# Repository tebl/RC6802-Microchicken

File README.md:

# RC6802 Microchicken

When starting out with retro computers, both fictional made homebrew or the commercial ones that were actually available for purchase in the 70s and 80s, there's one book in particular I've particularly enjoyed reading - that book is "22 micro-computer projects - to build, learn and learn" by Daniel Metzger (check out [ebay](http://ebay.com) or [abebooks.com](http://abebooks.com) for a copy). Written in 1985 on the tail-end of the homebrew computer-period, it gathers what I believe is the culmination of 10 years of teaching basic electronics, digital logic and computers to people without any prior knowledge for any of those things - perfect for me!

The book builds upon each chapter by building a computer based on the 6802-processor from Motorola, a mysteriously similar processor to the now far more popular 6502. While it might be seen as an odd choice for a main processor these days, even the most advanced circuits are easily adapted to the 6502 as well. Nearly every other book I've got in my bookshelf never seem to describe much past the basics, usually circuits for storage (tape-based), single-step circuits as well as using a Video Display Generator are details left for other books to fill - this is the only book I've got that actually shows how to implement them in an easy and understandable way.

The final projects in the book result in the Microchicken-computer, which I've adapted and laid out in the form of the RC6802 Microchicken computer. I have no idea why it's called the *Microchicken*, other than that the book author obviously had a peculiar sense of humour that I can't help but agree with. My current build of the computer is shown below, I also made a short [YouTube](https://www.youtube.com/watch?v=bi4SIbvGzfI)-clip where I push some of its buttons - a whole bunch of times!

The monitor software for the RC6802 Microchicken, like the hardware design itself, is also included in the aforementioned book. I've transcribed in and slightly adapted the assembly code so that it can be assembled using modern tools, the one I've chosen to use is [SB-Assembler 3](https://www.sbprojects.net/sbasm/) as it seems to support all of the 8bit CPUs I've managed to force upon it. For a further description on the various functions of the monitor and the firmware in , see its specific [README](https://github.com/tebl/RC6802-Microchicken/tree/master/software/firmware)-file as well. 

## Modules
As with most of my computer builds the computer have been split into two required main boards to stay under the magic 5$ cost limits over at [PCBWay](https://www.pcbway.com/setinvite.aspx?inviteid=88707) for each, a CPU board as well as a UI board sandwiched on top. There may be additional modules found among the project files, but the ones I've added here are the ones that have been considered ready.

| Module             | RC6802 Microchicken        | Expanded system | Order |
| ------------------ | -------------------------- | --------------- | ----- |
| [CPU](https://github.com/tebl/RC6802-Microchicken/tree/master/RC6802%20CPU) | required | required | [PCBWay](https://www.pcbway.com/project/shareproject/RC6802_Microchicken__CPU_module_revision_B_.html?inviteid=88707) |
| [User Interface](https://github.com/tebl/RC6802-Microchicken/tree/master/RC6802%20UI) | required | required | [PCBWay](https://www.pcbway.com/project/shareproject/RC6802_Microchicken__UI_module_revision_B_.html?inviteid=88707) |
| [Backplane](https://github.com/tebl/RC6502-Apple-1-Replica/tree/master/RC6502%20Backplane) | | required | [PCBWay](https://www.pcbway.com/project/shareproject/RC6502_Apple_1_Replica__Backplane_module_revision_A_.html?inviteid=88707) |
| [Prototyping module](https://github.com/tebl/RC6502-Apple-1-Replica/tree/master/RC6502%20Prototyping) | | optional | [PCBWay](https://www.pcbway.com/project/shareproject/RC6502_Apple_1_Replica__Module_prototyping_board_.html?inviteid=88707) |

As modules are constantly being worked on, I've also added an order link to the modules so that you can always get the last version I know works. Click the module name for more information about that specific module, including schematic and the list of parts you'd need to build it (BOM).

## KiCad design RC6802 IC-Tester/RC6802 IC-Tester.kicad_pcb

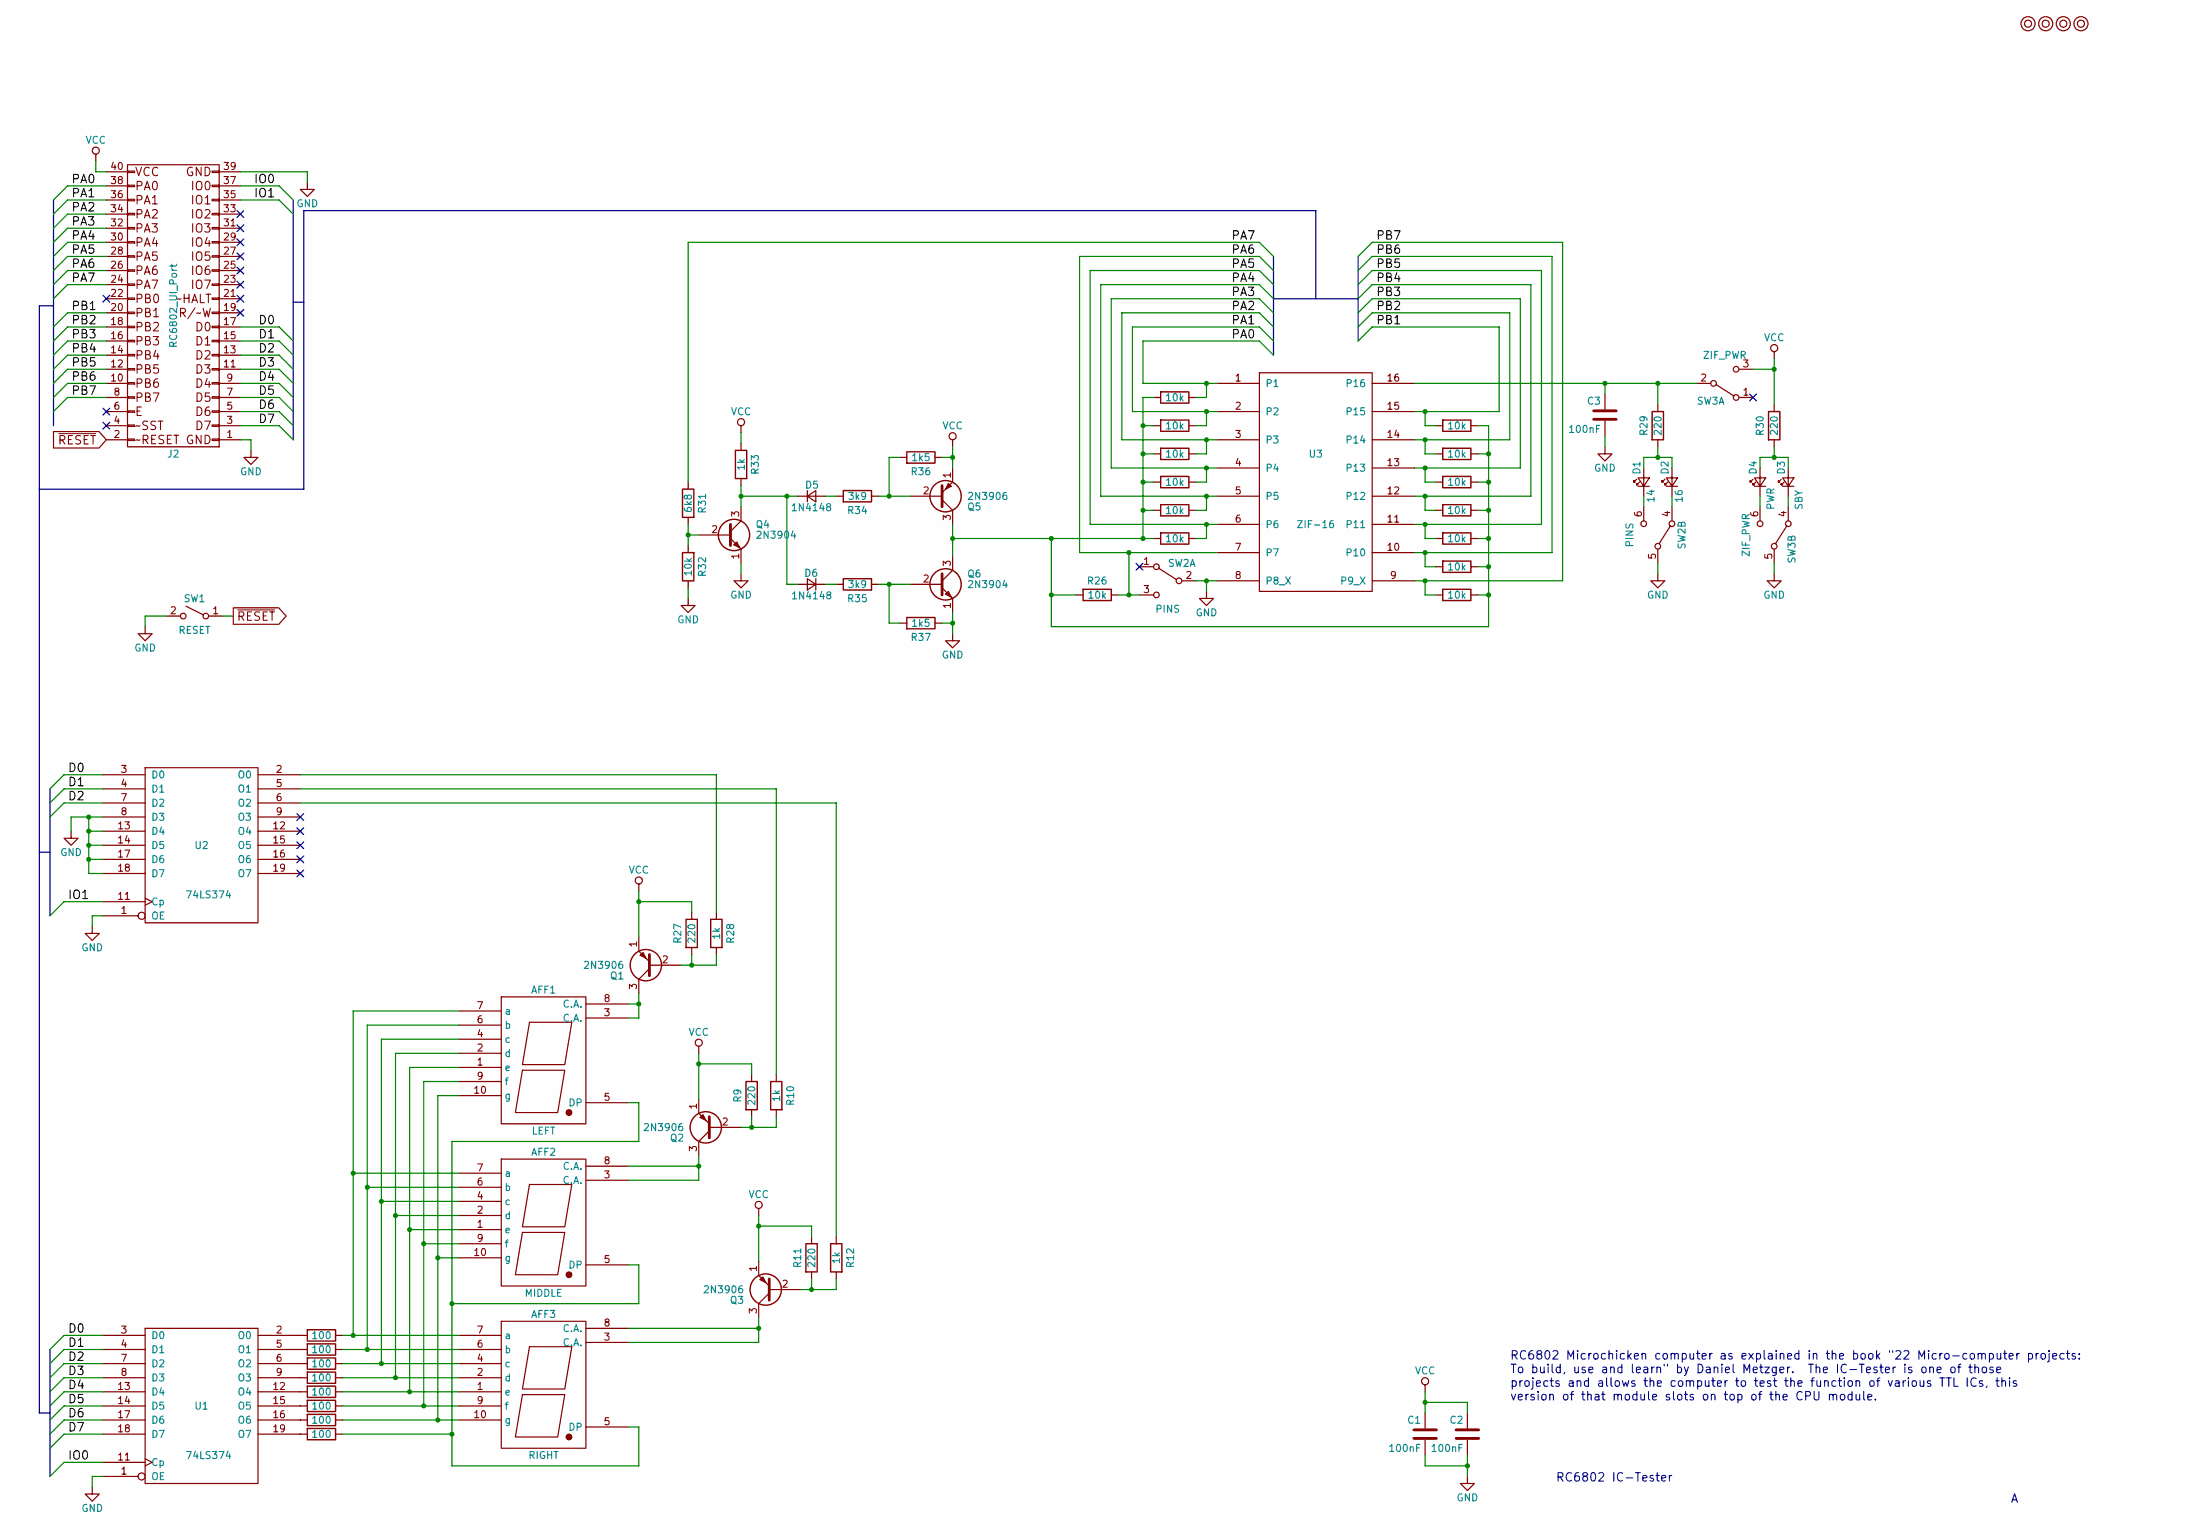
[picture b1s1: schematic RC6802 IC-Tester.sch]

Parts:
AFF1: LEFT; 7SegmentLED_LTS6760_LTS6780
AFF2: MIDDLE; 7SegmentLED_LTS6760_LTS6780
AFF3: RIGHT; 7SegmentLED_LTS6760_LTS6780
C1, C2, C3: 100nF; C_Disc_D4.7mm_W2.5mm_P5.00mm
D1: 14; LED_D5.0mm
D2: 16; LED_D5.0mm
D3: SBY; LED_D5.0mm
D4: PWR; LED_D5.0mm
D5, D6: 1N4148; D_DO-35_SOD27_P7.62mm_Horizontal
J2: RC6802_UI_Port; Pin_Header_Straight_2x20_Pitch2.54mm
M1, M2, M3, M4: Mounting; 1pin
Q1, Q2, Q3, Q5: 2N3906; TO-92_Molded_Narrow
Q4, Q6: 2N3904; TO-92_Molded_Narrow
R1, R2, R3, R4, R5, R6, R7, R8: 100; R_Axial_DIN0207_L6.3mm_D2.5mm_P10.16mm_Horizontal
R9, R11, R27, R29, R30: 220; R_Axial_DIN0207_L6.3mm_D2.5mm_P10.16mm_Horizontal
R10, R12, R28, R33: 1k; R_Axial_DIN0207_L6.3mm_D2.5mm_P10.16mm_Horizontal
R13, R14, R15, R16, R17, R18, R19, R20, R21, R22, R23, R24, R25, R26, R32: 10k; R_Axial_DIN0207_L6.3mm_D2.5mm_P10.16mm_Horizontal
R31: 6k8; R_Axial_DIN0207_L6.3mm_D2.5mm_P10.16mm_Horizontal
R34, R35: 3k9; R_Axial_DIN0207_L6.3mm_D2.5mm_P10.16mm_Horizontal
R36, R37: 1k5; R_Axial_DIN0207_L6.3mm_D2.5mm_P10.16mm_Horizontal
SW1: RESET; SW_PUSH_6mm
SW2: PINS; dpdt_switch_black
SW3: ZIF_PWR; dpdt_switch_black
U1, U2: 74LS374; DIP-20_W7.62mm_Socket
U3: ZIF-16

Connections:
/D0: J2.17, U1.3 (D0), U2.3 (D0)
/D1: J2.15, U1.4 (D1), U2.4 (D1)
/D2: J2.13, U1.7 (D2), U2.7 (D2)
/D3: J2.11, U1.8 (D3)
/D4: J2.9, U1.13 (D4)
/D5: J2.7, U1.14 (D5)
/D6: J2.5, U1.17 (D6)
/D7: J2.3, U1.18 (D7)
/IO0: J2.37, U1.11 (Cp)
/IO1: J2.35, U2.11 (Cp)
/PA0: J2.38, R13.1, U3.1
/PA1: J2.36, R14.1, U3.2
/PA2: J2.34, R15.1, U3.3
/PA3: J2.32, R16.1, U3.4
/PA4: J2.30, R17.1, U3.5
/PA5: J2.28, R18.1, U3.6
/PA6: J2.26, R26.1, SW2.3 (C), U3.7
/PA7: J2.24, R31.1
/PB1: J2.20, R19.2, U3.15
/PB2: J2.18, R20.2, U3.14
/PB3: J2.16, R21.2, U3.13
/PB4: J2.14, R22.2, U3.12
/PB5: J2.12, R23.2, U3.11
/PB6: J2.10, R24.2, U3.10
/PB7: J2.8, R25.2, U3.9 (P9_X)
GND: C1.2, C2.2, C3.2, J2.1, J2.39, Q4.1 (E), Q6.1 (E), R32.1, R37.1, SW1.2 (B), SW2.2 (B), SW2.5 (B), SW3.5 (B), U1.1 (OE), U1.10 (GND), U2.1 (OE), U2.8 (D3), U2.10 (GND), U2.13 (D4), U2.14 (D5), U2.17 (D6), U2.18 (D7), U3.8 (P8_X)
unnamed: AFF1.1 (e), AFF2.1 (e), AFF3.1 (e), R5.1
unnamed: AFF1.2 (d), AFF2.2 (d), AFF3.2 (d), R4.1
unnamed: AFF1.3 (C.A.), AFF1.8 (C.A.), Q1.3 (C)
unnamed: AFF1.4 (c), AFF2.4 (c), AFF3.4 (c), R3.1
unnamed: AFF1.5 (DP), AFF2.5 (DP), AFF3.5 (DP), R8.1
unnamed: AFF1.6 (b), AFF2.6 (b), AFF3.6 (b), R2.1
unnamed: AFF1.7 (a), AFF2.7 (a), AFF3.7 (a), R1.1
unnamed: AFF1.9 (f), AFF2.9 (f), AFF3.9 (f), R6.1
unnamed: AFF1.10 (g), AFF2.10 (g), AFF3.10 (g), R7.1
unnamed: AFF2.3 (C.A.), AFF2.8 (C.A.), Q2.3 (C)
unnamed: AFF3.3 (C.A.), AFF3.8 (C.A.), Q3.3 (C)
unnamed: C3.1, R29.1, SW3.2 (B), U3.16
unnamed: D1.1 (K), SW2.6 (C)
unnamed: D1.2 (A), D2.2 (A), R29.2
unnamed: D2.1 (K), SW2.4 (A)
unnamed: D3.1 (K), SW3.4 (A)
unnamed: D3.2 (A), D4.2 (A), R30.2
unnamed: D4.1 (K), SW3.6 (C)
unnamed: D5.1 (K), D6.2 (A), Q4.3 (C), R33.2
unnamed: D5.2 (A), R34.2
unnamed: D6.1 (K), R35.1
unnamed: Q1.2 (B), R27.2, R28.2
unnamed: Q2.2 (B), R9.2, R10.2
unnamed: Q3.2 (B), R11.2, R12.2
unnamed: Q4.2 (B), R31.2, R32.2
unnamed: Q5.2 (B), R34.1, R36.2
unnamed: Q5.3 (C), Q6.3 (C), R13.2, R14.2, R15.2, R16.2, R17.2, R18.2, R19.1, R20.1, R21.1, R22.1, R23.1, R24.1, R25.1, R26.2
unnamed: Q6.2 (B), R35.2, R37.2
unnamed: R1.2, U1.2 (O0)
unnamed: R2.2, U1.5 (O1)
unnamed: R3.2, U1.6 (O2)
unnamed: R4.2, U1.9 (O3)
unnamed: R5.2, U1.12 (O4)
unnamed: R6.2, U1.15 (O5)
unnamed: R7.2, U1.16 (O6)
unnamed: R8.2, U1.19 (O7)
unnamed: R10.1, U2.5 (O1)
unnamed: R12.1, U2.6 (O2)
unnamed: R28.1, U2.2 (O0)
VCC: C1.1, C2.1, J2.40, Q1.1 (E), Q2.1 (E), Q3.1 (E), Q5.1 (E), R9.1, R11.1, R27.1, R30.1, R33.1, R36.1, SW3.3 (C), U1.20 (VCC), U2.20 (VCC)
~RESET: J2.2, SW1.1 (A)

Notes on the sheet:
RC6802 IC-Tester
RC6802 Microchicken computer as explained in the book "22 Micro-computer projects: To build, use and learn" by Daniel Metzger. The IC-Tester is one of those projects and allows the computer to test the function of various TTL ICs, this version of that module slots on top of the CPU module.

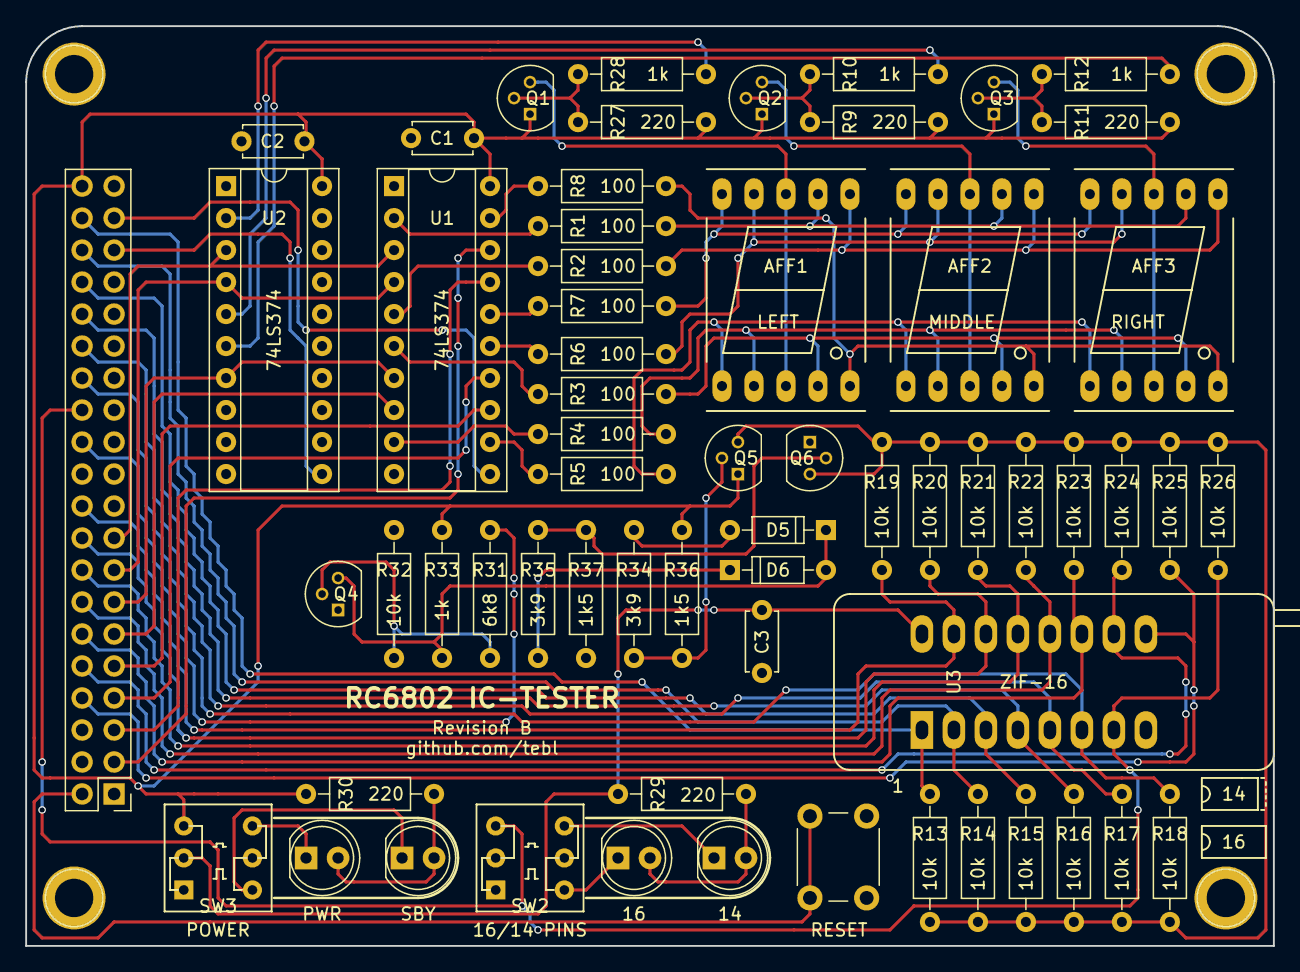
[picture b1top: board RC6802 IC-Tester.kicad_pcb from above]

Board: 2 copper layers, 99.1 x 73.0 mm, 66 parts (0 on the bottom side), 67 nets.

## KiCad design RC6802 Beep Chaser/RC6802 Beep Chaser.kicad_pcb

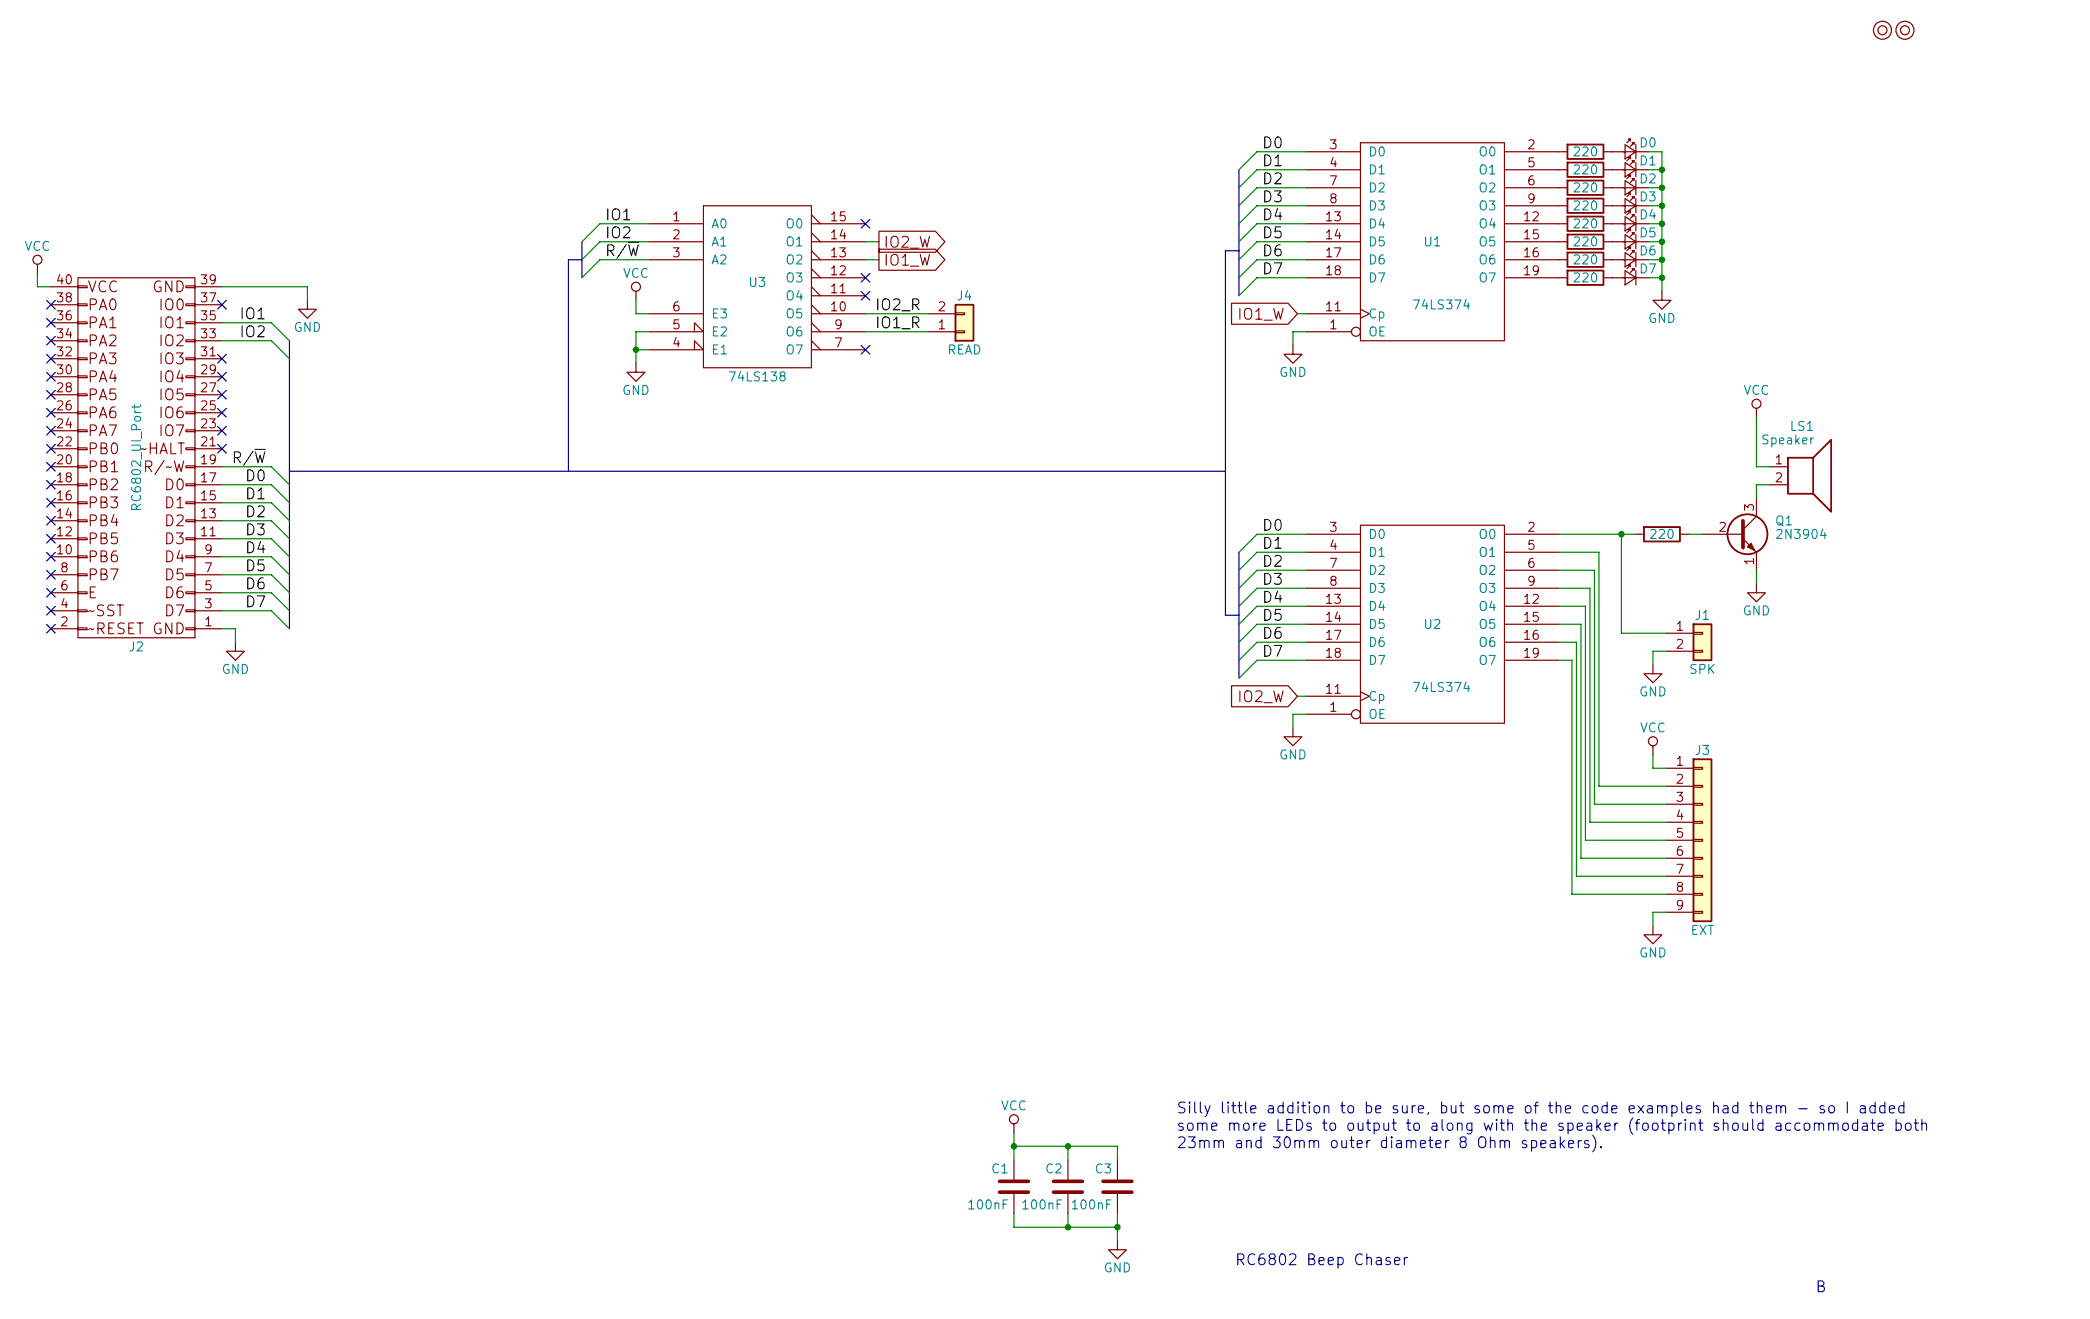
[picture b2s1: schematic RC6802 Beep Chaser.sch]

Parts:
C1, C2, C3: 100nF; C_Disc_D4.7mm_W2.5mm_P5.00mm
D0, D1, D2, D3, D4, D5, D6, D7: LED; LED_D5.0mm
J1: SPK; Pin_Header_Straight_1x02_Pitch2.54mm
J2: RC6802_UI_Port; Pin_Header_Straight_2x20_Pitch2.54mm
J3: EXT; Pin_Header_Straight_1x09_Pitch2.54mm
J4: READ; Pin_Header_Straight_1x02_Pitch2.54mm
LS1: Speaker; Mini_Speaker
M3, M4: Mounting; 1pin
Q1: 2N3904; TO-92_Inline_Wide
R1, R4, R5, R6, R7, R8, R9, R10, R11: 220; R_Axial_DIN0207_L6.3mm_D2.5mm_P10.16mm_Horizontal
U1, U2: 74LS374; DIP-20_W7.62mm_Socket
U3: 74LS138; DIP-16_W7.62mm_Socket

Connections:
/D0: J2.17, U1.3 (D0), U2.3 (D0)
/D1: J2.15, U1.4 (D1), U2.4 (D1)
/D2: J2.13, U1.7 (D2), U2.7 (D2)
/D3: J2.11, U1.8 (D3), U2.8 (D3)
/D4: J2.9, U1.13 (D4), U2.13 (D4)
/D5: J2.7, U1.14 (D5), U2.14 (D5)
/D6: J2.5, U1.17 (D6), U2.17 (D6)
/D7: J2.3, U1.18 (D7), U2.18 (D7)
/IO1: J2.35, U3.1 (A0)
/IO1_R: J4.1, U3.9 (O6)
/IO2: J2.33, U3.2 (A1)
/IO2_R: J4.2, U3.10 (O5)
/R/~W: J2.19, U3.3 (A2)
GND: C1.2, C2.2, C3.2, D0.1 (K), D1.1 (K), D2.1 (K), D3.1 (K), D4.1 (K), D5.1 (K), D6.1 (K), D7.1 (K), J1.2, J2.1, J2.39, J3.9, Q1.1 (E), U1.1 (OE), U1.10 (GND), U2.1 (OE), U2.10 (GND), U3.4 (E1), U3.5 (E2), U3.8 (GND)
IO1_W: U1.11 (Cp), U3.13 (O2)
IO2_W: U2.11 (Cp), U3.14 (O1)
unnamed: D0.2 (A), R4.1
unnamed: D1.2 (A), R5.1
unnamed: D2.2 (A), R6.1
unnamed: D3.2 (A), R7.1
unnamed: D4.2 (A), R8.1
unnamed: D5.2 (A), R9.1
unnamed: D6.2 (A), R10.1
unnamed: D7.2 (A), R11.1
unnamed: J1.1, R1.2, U2.2 (O0)
unnamed: J3.2, U2.5 (O1)
unnamed: J3.3, U2.6 (O2)
unnamed: J3.4, U2.9 (O3)
unnamed: J3.5, U2.12 (O4)
unnamed: J3.6, U2.15 (O5)
unnamed: J3.7, U2.16 (O6)
unnamed: J3.8, U2.19 (O7)
unnamed: LS1.2, Q1.3 (C)
unnamed: Q1.2 (B), R1.1
unnamed: R4.2, U1.2 (O0)
unnamed: R5.2, U1.5 (O1)
unnamed: R6.2, U1.6 (O2)
unnamed: R7.2, U1.9 (O3)
unnamed: R8.2, U1.12 (O4)
unnamed: R9.2, U1.15 (O5)
unnamed: R10.2, U1.16 (O6)
unnamed: R11.2, U1.19 (O7)
VCC: C1.1, C2.1, C3.1, J2.40, J3.1, LS1.1, U1.20 (VCC), U2.20 (VCC), U3.6 (E3), U3.16 (VCC)

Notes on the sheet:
RC6802 Beep Chaser
Silly little addition to be sure, but some of the code examples had them - so I added some more LEDs to output to along with the speaker (footprint should accommodate both 23mm and 30mm outer diameter 8 Ohm speakers).

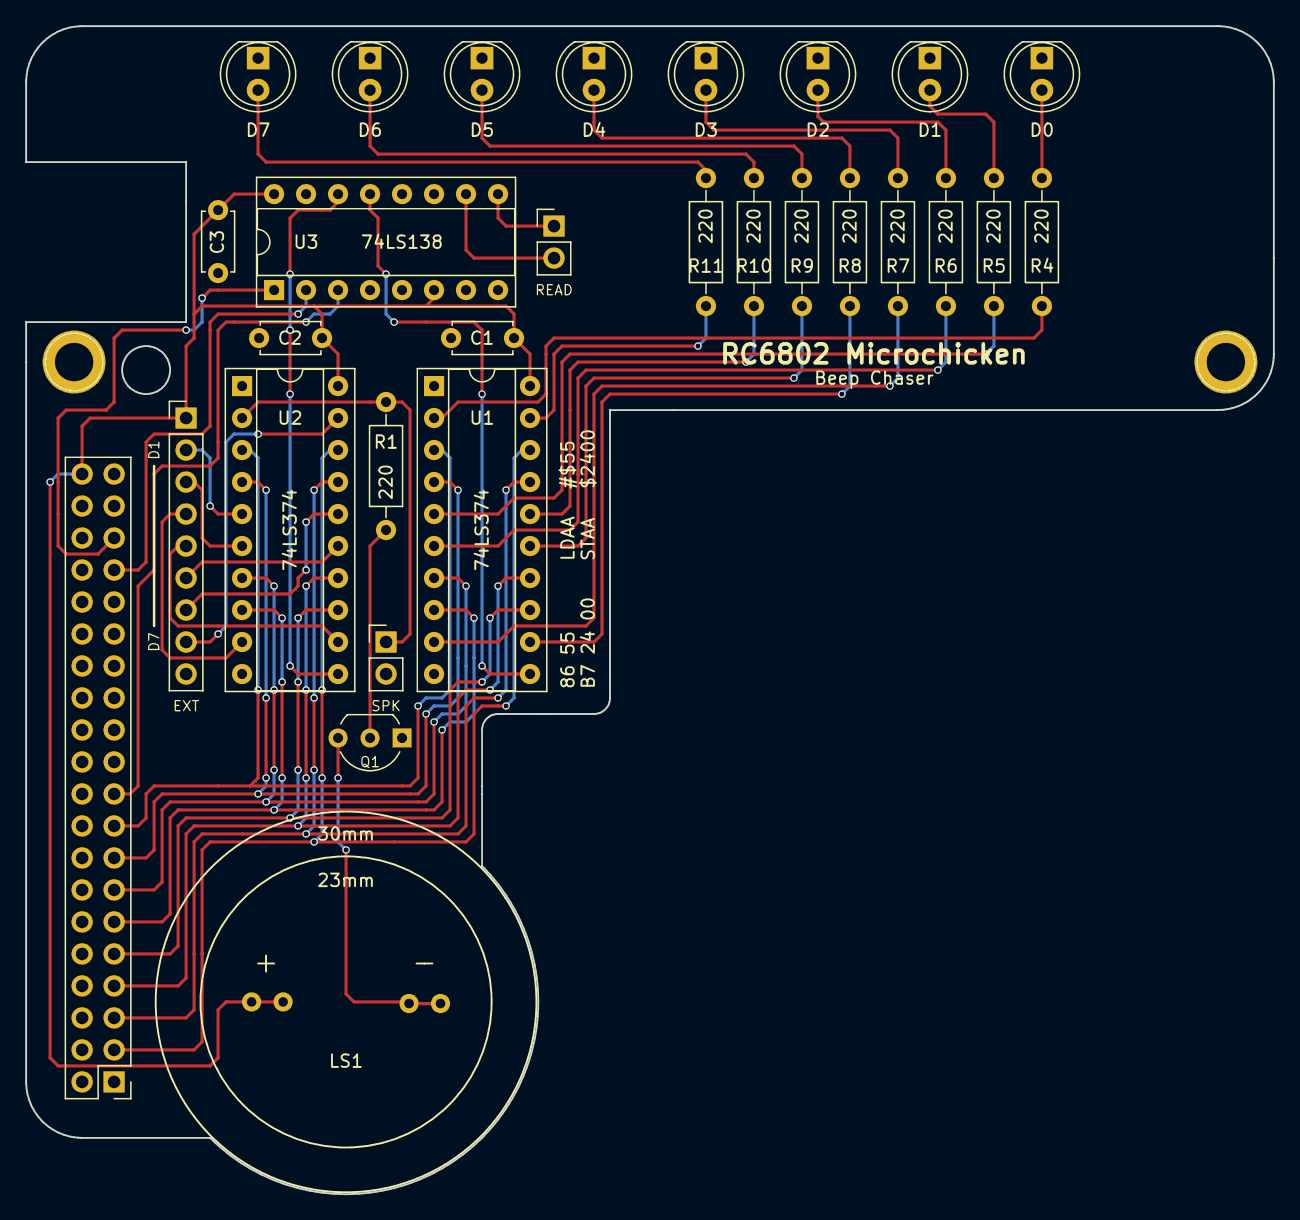
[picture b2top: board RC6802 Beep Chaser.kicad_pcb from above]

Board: 2 copper layers, 99.1 x 92.7 mm, 31 parts (0 on the bottom side), 43 nets.

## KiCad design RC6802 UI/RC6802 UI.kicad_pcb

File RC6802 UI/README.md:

# RC6802 Microchicken

One of my most enjoyable reads the past year has been "22 micro-computer projects - to build, learn and learn" by Daniel L. Metzger, the Microchicken-computer is described in detail within it and so I sought to build one myself. The computer has been designed as a set of smaller modules, for an overall description a listing of the available modules - see the main project [README](https://github.com/tebl/RC6802-Microchicken)!

## User Interface
The User Interface module has been designed to stack on top of the CPU-module, doing it this way the overall project stays within manageable PCB-costs and should be buildable for anyone with a reasonable set of tools available. An assembled version of the CPU-module by itself as well as a version stacked underneath the User Interface module can be seen below.

The User Interface has two 7-segment displays as well as a 16-key keypad, all of the keypad pins have also been brought out to a separate connector so that an external keypad can also be used instead of the onboard-one (easier when using the computer with a backplane and additional expansions). It has an implementation of the described SST-circuit for the 6802 processor as well as being able to latch the IRQ-line permanently low, this is used by the monitor as a software-based alternative for stepping through code.

Additionally a circuit for loading and saving data using audio tapes is also available as an option, I only had room to add the one audio connector so I used a single 3.5mm connector instead. I used the same pinouts as on the ZX Spectrum +3, so the same tape cables can be used with the RC6802 and you should be able to find a new set of these cables via ebay as they are still being made today.

# Schematic
The supplied KiCad files should be sufficient as both a schematic and as a starting point for ordering PCBs (basically you could just zip the contents of the export folder and upload that on a fabrication site), the schematic is also available in [PDF-format](https://github.com/tebl/RC6802-Microchicken/raw/master/RC6802%20UI/export/RC6802%20UI.pdf) so that you print it out and hang it on your office wall, excellent conversation starter at any technology-oriented business worth working at (or so I keep telling myself)!

If you require more assistance, there is also a separate [Troubleshooting](https://github.com/tebl/RC6802-Microchicken/blob/master/Troubleshooting.md) guide as part of the supplied documentation. Also make sure to have a read through the [Manual](https://github.com/tebl/RC6802-Microchicken/blob/master/Manual.md) to see if it's a *feature* instead! Some of these documents may not actually exist at the time of clicking on them.

# BOM
This is the part list as it stands now, most should be easy to get a hold of from your local electronic component shop though you might have to consider other sources depending on the quality of your local vendor. Values in parenthesis are optional components that might not be needed (mainly the tape interface and the SST-circuit).

Some vendors will have the same ICs in different form factors, the ones you want will often be specified as being in the form of a DIP/PDIP package - usually you'll want sockets for each of them as well. For the pin headers, you probably won't find the exact pin count so just buy the 40 pin versions and snip off the parts you don't need.

| Reference       | Item                                  | Count |
| --------------- | ------------------------------------- | ----- |
| PCB             | Fabricate yourself using Gerber files |     1 |
| AFF1-AFF2       | 0.56" 7-segment displays (C.A.)       |     2 |
| C1-C3           | 100nF ceramic capacitor               |     3 |
| C4,C6           | 50nF ceramic capacitor                |    (2)|
| C5              | 68nF ceramic capacitor                |    (1)|
| C8              | 100nF ceramic capacitor               |    (1)|
| D1              | 5mm LED                               |    (1)|
| D2-D4           | 1N4148 small signal diode             |    (3)|
| J1 Audio        | 3.5mm 5pin green audio socket (PJ307) |    (1)|
| J2              | 2x20 female header pins *             |     1 |
| J3              | 2x5 right-angle header pins           |    (1)|
| Q1-Q2           | 2N3906 TO-92 transistor               |     2 |
| Q3-Q5           | 2N3904 TO-92 transistor               |    (3)|
| R13             | 100 ohm resistor                      |    (1)|
| R27,R29         | 220 ohm resistor                      |     2 |
| R28,R30         | 1k (1000) ohm resistor                |     2 |
| R19-R21         | 1k ohm resistor                       |    (3)|
| R14,R23         | 1k5 (1500) ohm resistor               |    (2)|
| R1-R4           | 4k7 (4700) ohm resistor               |     4 |
| R26             | 2k2 (2200) ohm resistor               |    (1)|
| R17             | 2k7 (2700) ohm resistor               |    (1)|
| R22             | 6k8 (6800) ohm resistor               |    (1)|
| R12,R18,R24     | 10k ohm resistor                      |    (3)|
| R25             | 51k ohm resistor                      |    (1)|
| SW1,SW3-SW18    | Momentary push button                 |    17 |
| SW2,SW19,SW21   | 6pin 8.5mm x 8.5mm latching switch    |    (3)|
| SW20            | 6pin 8.5mm x 8.5mm non-latching switch|    (1)|
| U1              | 74LS374 (DIP-20)                      |     1 |
| U2              | 74LS00 (DIP-14)                       |     1 |
| U3              | 74LS73 (DIP-14)                       |    (1)|
|                 | M3 nylon hex standoffs **             |     4 |
|                 | M3 nylon screws **                    |     4 |
|                 | M3 nylon nuts **                      |     4 |

*) An ordinary set of 2x20 female header pins can be installed on the reverse-side, but since the connector has quite a few signals that could be used for your own projects later I recommend getting ones with the longer pins - these are most oftenly found listed as a stacking Raspberry Pi header. Slot onto CPU-module using M3 standoffs before soldering to get the spacing correct.

**) The length of the nylon standoffs depend on the female header pins used, extra length (M3x12mm) or the ordinary non-stacking variant (M3x10mm). Better yet, get one of those $4 M3 Nylon Stand-off sets from China - that way you're all set for a few projects down the road as well.

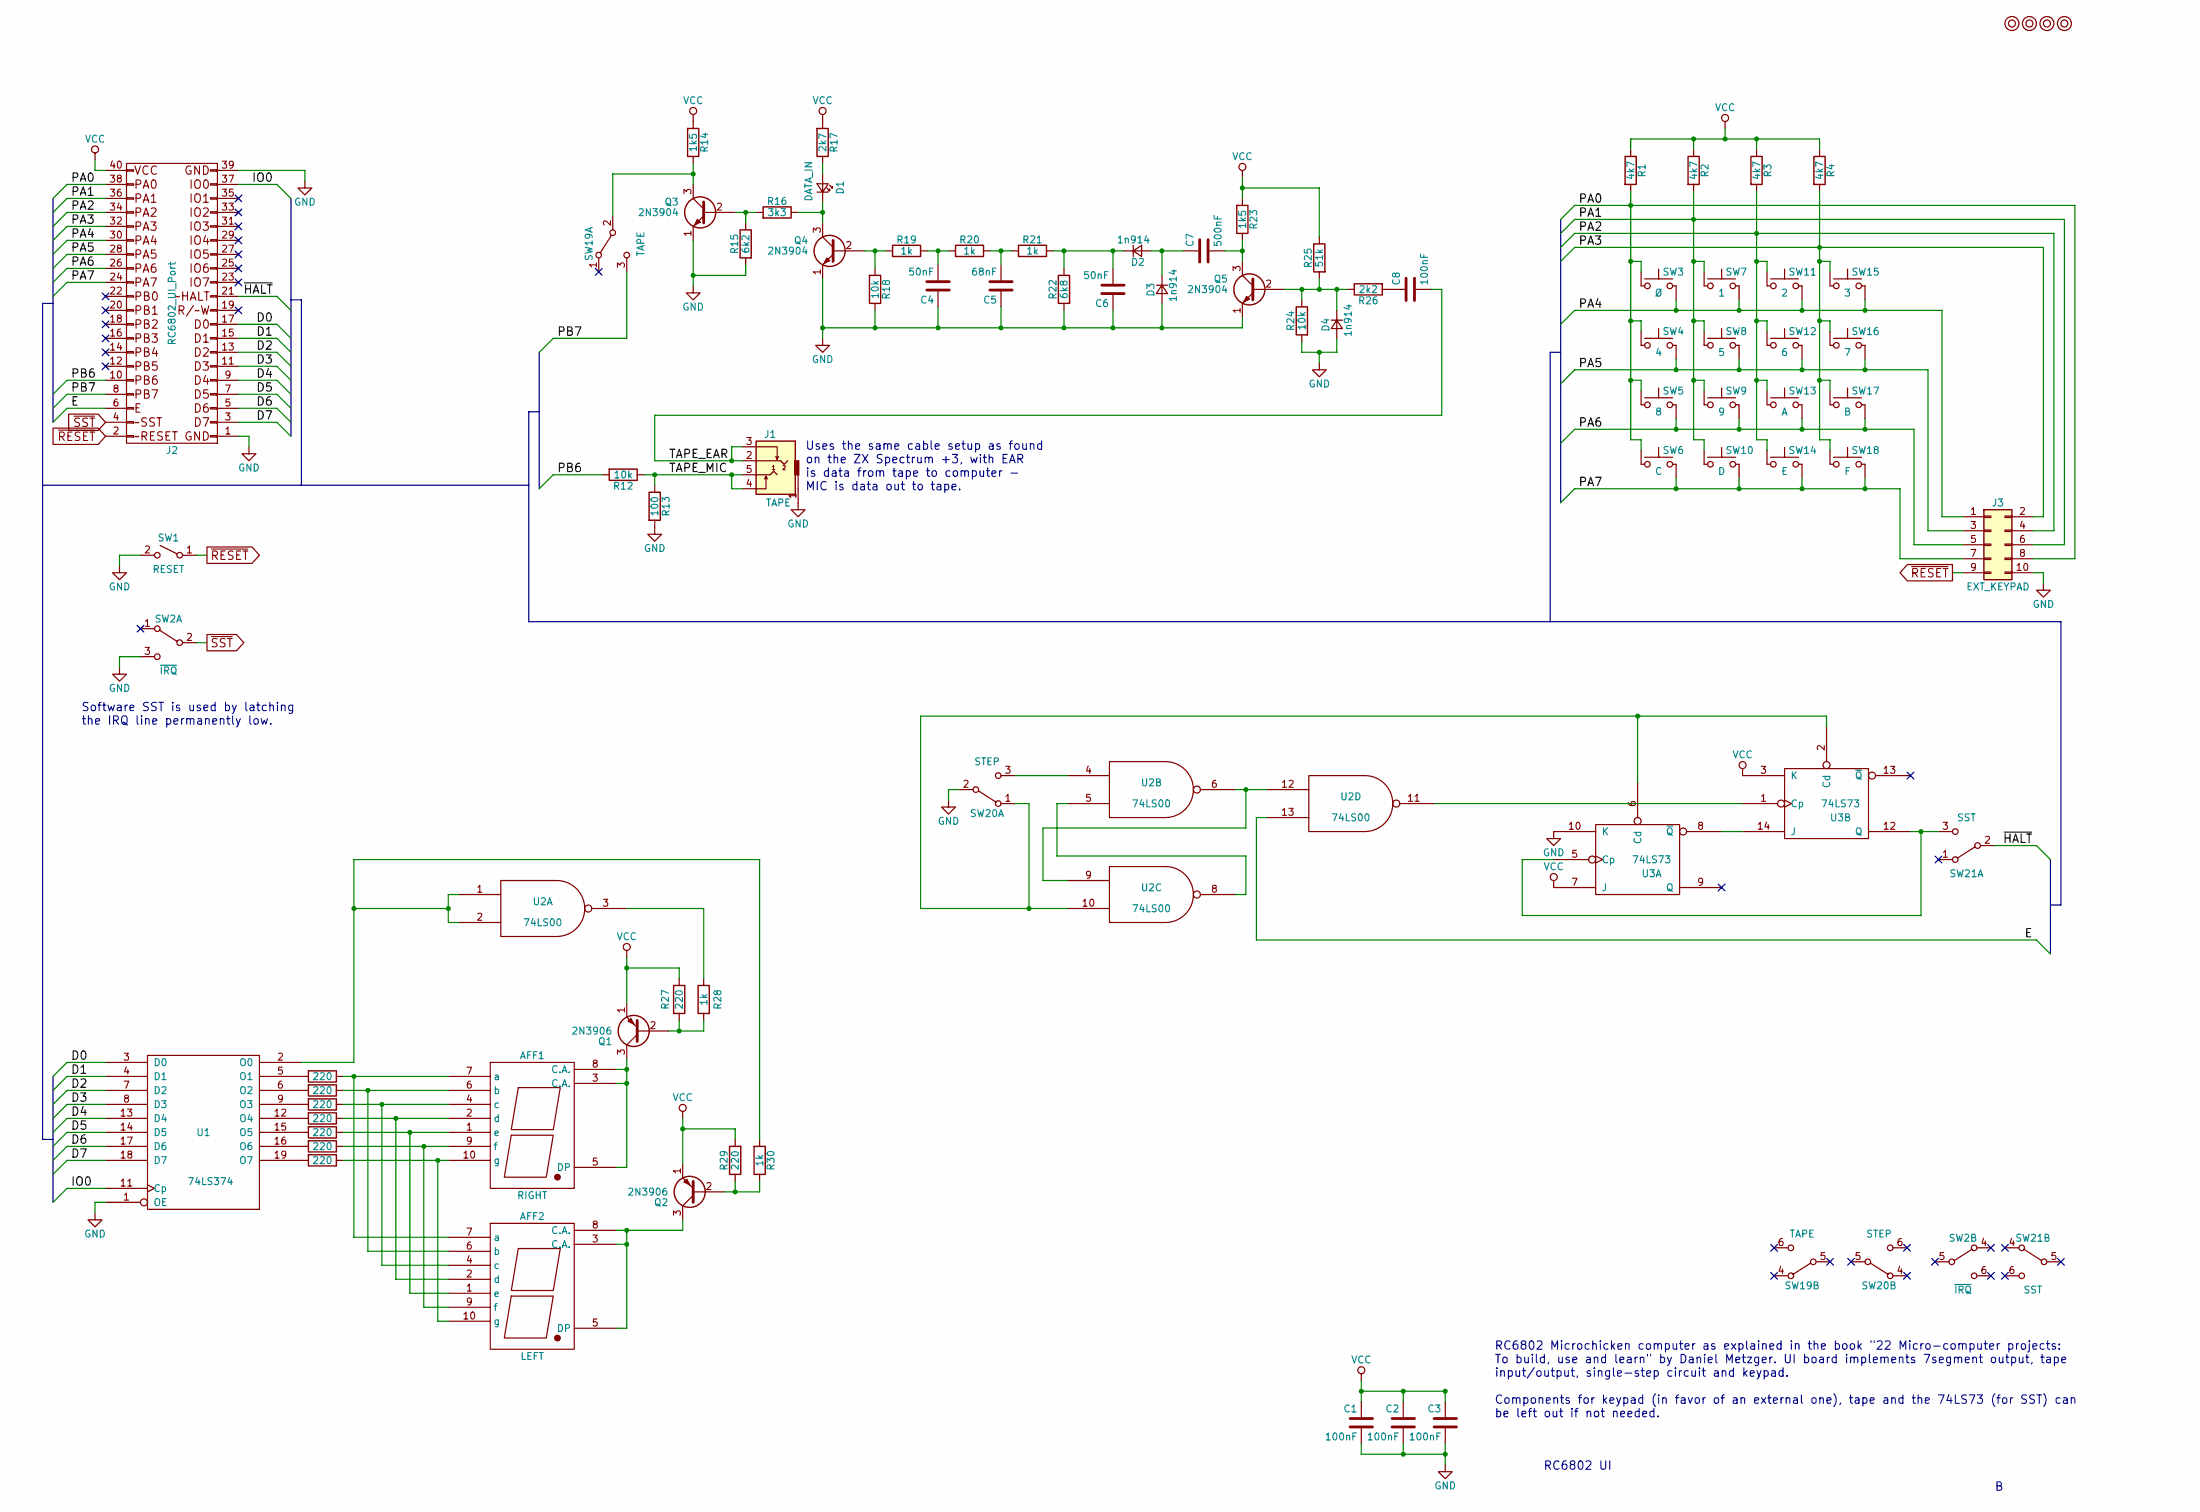
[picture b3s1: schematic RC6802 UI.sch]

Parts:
AFF1: RIGHT; 7SegmentLED_LTS6760_LTS6780
AFF2: LEFT; 7SegmentLED_LTS6760_LTS6780
C1, C2, C3, C8: 100nF; C_Disc_D4.7mm_W2.5mm_P5.00mm
C4, C6: 50nF; C_Disc_D4.7mm_W2.5mm_P5.00mm
C5: 68nF; C_Disc_D4.7mm_W2.5mm_P5.00mm
C7: 500nF; C_Disc_D4.7mm_W2.5mm_P5.00mm
D1: DATA_IN; LED_D5.0mm
D2, D3, D4: 1n914; D_DO-35_SOD27_P7.62mm_Horizontal
J1: TAPE; Tayda_3.5mm_stereo_TRS_jack_A-853
J2: RC6802_UI_Port; Pin_Header_Straight_2x20_Pitch2.54mm
J3: EXT_KEYPAD; Pin_Header_Angled_2x05_Pitch2.54mm
M1, M2, M3, M4: Mounting; 1pin
Q1, Q2: 2N3906; TO-92_Molded_Narrow
Q3, Q4, Q5: 2N3904; TO-92_Molded_Narrow
R1, R2, R3, R4: 4k7; R_Axial_DIN0207_L6.3mm_D2.5mm_P10.16mm_Horizontal
R5, R6, R7, R8, R9, R10, R11, R27, R29: 220; R_Axial_DIN0207_L6.3mm_D2.5mm_P10.16mm_Horizontal
R12, R18, R24: 10k; R_Axial_DIN0207_L6.3mm_D2.5mm_P10.16mm_Horizontal
R13: 100; R_Axial_DIN0207_L6.3mm_D2.5mm_P10.16mm_Horizontal
R14, R23: 1k5; R_Axial_DIN0207_L6.3mm_D2.5mm_P10.16mm_Horizontal
R15: 6k2; R_Axial_DIN0207_L6.3mm_D2.5mm_P10.16mm_Horizontal
R16: 3k3; R_Axial_DIN0207_L6.3mm_D2.5mm_P10.16mm_Horizontal
R17: 2k7; R_Axial_DIN0207_L6.3mm_D2.5mm_P10.16mm_Horizontal
R19, R20, R21, R28, R30: 1k; R_Axial_DIN0207_L6.3mm_D2.5mm_P10.16mm_Horizontal
R22: 6k8; R_Axial_DIN0207_L6.3mm_D2.5mm_P10.16mm_Horizontal
R25: 51k; R_Axial_DIN0207_L6.3mm_D2.5mm_P10.16mm_Horizontal
R26: 2k2; R_Axial_DIN0207_L6.3mm_D2.5mm_P10.16mm_Horizontal
SW1: RESET; SW_PUSH_6mm
SW2: ~IRQ; dpdt_switch_black
SW3: Ø; SW_PUSH_6mm
SW4: 4; SW_PUSH_6mm
SW5: 8; SW_PUSH_6mm
SW6: C; SW_PUSH_6mm
SW7: 1; SW_PUSH_6mm
SW8: 5; SW_PUSH_6mm
SW9: 9; SW_PUSH_6mm
SW10: D; SW_PUSH_6mm
SW11: 2; SW_PUSH_6mm
SW12: 6; SW_PUSH_6mm
SW13: A; SW_PUSH_6mm
SW14: E; SW_PUSH_6mm
SW15: 3; SW_PUSH_6mm
SW16: 7; SW_PUSH_6mm
SW17: B; SW_PUSH_6mm
SW18: F; SW_PUSH_6mm
SW19: TAPE; dpdt_switch_black
SW20: STEP; dpdt_switch_black
SW21: SST; dpdt_switch_black
U1: 74LS374; DIP-20_W7.62mm_Socket
U2: 74LS00; DIP-14_W7.62mm_Socket
U3: 74LS73; DIP-14_W7.62mm_Socket

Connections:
/D0: J2.17, U1.3 (D0)
/D1: J2.15, U1.4 (D1)
/D2: J2.13, U1.7 (D2)
/D3: J2.11, U1.8 (D3)
/D4: J2.9, U1.13 (D4)
/D5: J2.7, U1.14 (D5)
/D6: J2.5, U1.17 (D6)
/D7: J2.3, U1.18 (D7)
/E: J2.6, U2.13
/IO0: J2.37, U1.11 (Cp)
/PA0: J2.38, J3.8, R1.2, SW3.1, SW4.1, SW5.1, SW6.1
/PA1: J2.36, J3.6, R2.2, SW7.1, SW8.1, SW9.1, SW10.1
/PA2: J2.34, J3.4, R3.2, SW11.1, SW12.1, SW13.1, SW14.1
/PA3: J2.32, J3.2, R4.2, SW15.1, SW16.1, SW17.1, SW18.1
/PA4: J2.30, J3.1, SW3.2, SW7.2, SW11.2, SW15.2
/PA5: J2.28, J3.3, SW4.2, SW8.2, SW12.2, SW16.2
/PA6: J2.26, J3.5, SW5.2, SW9.2, SW13.2, SW17.2
/PA7: J2.24, J3.7, SW6.2, SW10.2, SW14.2, SW18.2
/PB6: J2.10, R12.2
/PB7: J2.8, SW19.3 (C)
/TAPE_EAR: C8.2, J1.2, J1.3
/TAPE_MIC: J1.4, J1.5, R12.1, R13.1
/~HALT: J2.21, SW21.2 (B)
GND: C1.2, C2.2, C3.2, C4.1, C5.1, C6.1, D3.2 (A), D4.2 (A), J1.1, J2.1, J2.39, J3.10, Q3.1 (E), Q4.1 (E), Q5.1 (E), R13.2, R15.2, R18.1, R22.2, R24.2, SW1.2 (B), SW2.3 (C), SW20.2 (B), U1.1 (OE), U1.10 (GND), U2.7 (GND), U3.10 (K), U3.11 (GND)
unnamed: AFF1.1 (e), AFF2.1 (e), R9.1
unnamed: AFF1.2 (d), AFF2.2 (d), R8.1
unnamed: AFF1.3 (C.A.), AFF1.5 (DP), AFF1.8 (C.A.), Q1.3 (C)
unnamed: AFF1.4 (c), AFF2.4 (c), R7.1
unnamed: AFF1.6 (b), AFF2.6 (b), R6.1
unnamed: AFF1.7 (a), AFF2.7 (a), R5.1
unnamed: AFF1.9 (f), AFF2.9 (f), R10.1
unnamed: AFF1.10 (g), AFF2.10 (g), R11.1
unnamed: AFF2.3 (C.A.), AFF2.5 (DP), AFF2.8 (C.A.), Q2.3 (C)
unnamed: C4.2, R19.1, R20.2
unnamed: C5.2, R20.1, R21.2
unnamed: C6.2, D2.1 (K), R21.1, R22.1
unnamed: C7.1, D2.2 (A), D3.1 (K)
unnamed: C7.2, Q5.3 (C), R23.1
unnamed: C8.1, R26.2
unnamed: D1.1 (K), Q4.3 (C), R16.1
unnamed: D1.2 (A), R17.1
unnamed: D4.1 (K), Q5.2 (B), R24.1, R25.2, R26.1
unnamed: Q1.2 (B), R27.2, R28.2
unnamed: Q2.2 (B), R29.1, R30.1
unnamed: Q3.2 (B), R15.1, R16.2
unnamed: Q3.3 (C), R14.1, SW19.2 (B)
unnamed: Q4.2 (B), R18.2, R19.2
unnamed: R5.2, U1.5 (O1)
unnamed: R6.2, U1.6 (O2)
unnamed: R7.2, U1.9 (O3)
unnamed: R8.2, U1.12 (O4)
unnamed: R9.2, U1.15 (O5)
unnamed: R10.2, U1.16 (O6)
unnamed: R11.2, U1.19 (O7)
unnamed: R28.1, U2.3
unnamed: R30.2, U1.2 (O0), U2.1, U2.2
unnamed: SW20.1 (A), U2.10, U3.2 (Cd), U3.6 (Cd)
unnamed: SW20.3 (C), U2.4
unnamed: SW21.3 (C), U3.5 (Cp), U3.12 (Q)
unnamed: U2.5, U2.8
unnamed: U2.11, U3.1 (Cp)
unnamed: U2.6, U2.9, U2.12
unnamed: U3.8 (~Q), U3.14 (J)
VCC: C1.1, C2.1, C3.1, J2.40, Q1.1 (E), Q2.1 (E), R1.1, R2.1, R3.1, R4.1, R14.2, R17.2, R23.2, R25.1, R27.1, R29.2, U1.20 (VCC), U2.14 (VCC), U3.3 (K), U3.4 (VCC), U3.7 (J)
~RESET: J2.2, J3.9, SW1.1 (A)
~SST: J2.4, SW2.2 (B)

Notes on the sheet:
RC6802 UI
Uses the same cable setup as found on the ZX Spectrum +3, with EAR is data from tape to computer - MIC is data out to tape.
Software SST is used by latching the IRQ line permanently low.
RC6802 Microchicken computer as explained in the book "22 Micro-computer projects: To build, use and learn" by Daniel Metzger. UI board implements 7segment output, tape input/output, single-step circuit and keypad. Components for keypad (in favor of an external one), tape and the 74LS73 (for SST) c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
